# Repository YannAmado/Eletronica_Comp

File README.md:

# Projeto fonte com seletor de tensão
Yann Amado Nunes Costa : 10746943

Matéria : Eletrônica para Computação

Docente : Eduardo do Valles Simões

## Tabela de preços : 

| Peça                |  Preço              |
| ------------------- | ------------------- |
|  Transformador 220v-24v | R$41,00 |
|  Diodo 1N 4004 |  6xR$0,15 |
|       Capacitor 330uFx25V              |      R$0,34              |
|       Capacitor 470uFx25V              |      R$0,33              |
|       Capacitor 1.0uFx50V              |            3xR$0,10           |
|           Resistor 750Ohms          |      R$0,15               |
|           Resistor 150Ohms          |      R$0,20               |
|        LM317             |    R$7,50                 |
|   Potenciômetro Linear 1KΩ             |    R$1,99                 |

Obs : Os resistores foram escolhidos seguindo a formula provida pelo datasheet do LM317

## Simulação do Circuito no Falstad:

Imagem do circuito feito no falstad

link para o circuito : http://tinyurl.com/y8s6mfzf

## Esquemática e PCB

Todos os circuitos estão disponíveis dentro da página : https://github.com/YannAmado/Eletronica_Comp

- Imagem da esquemática feita no eagle

- Imagem do PCB feito no eagle

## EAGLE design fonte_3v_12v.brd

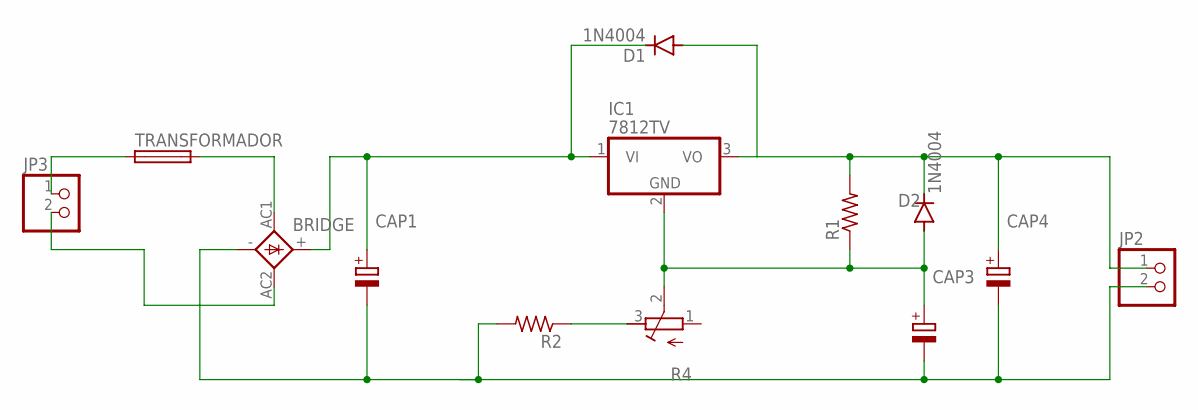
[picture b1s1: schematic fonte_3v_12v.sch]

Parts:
BRIDGE: 2KBB-R
CAP1, CAP3, CAP4: CPOL-EUE5-13; E5-13
D1, D2: 1N4004; DO41-10
IC1: 7812TV; TO220V
JP2, JP3: PINHD-1X2; 1X02
R1, R2: R-US_0204/7; 0204/7
R4: R-TRIMM3339P; RTRIM3339P
TRANSFORMADOR: SH22,5

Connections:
unnamed: JP3.1, TRANSFORMADOR.1
unnamed: BRIDGE.AC1, TRANSFORMADOR.2
unnamed: CAP4.+, D1.A, D2.C, IC1.3 (VO), JP2.1, R1.2
unnamed: BRIDGE.AC2, JP3.2
unnamed: BRIDGE.+, CAP1.+, D1.C, IC1.1 (VI)
unnamed: R2.1, R4.3 (E)
unnamed: BRIDGE.-, CAP1.-, CAP3.-, CAP4.-, JP2.2, R2.2
unnamed: CAP3.+, D2.A, IC1.2 (GND), R1.1, R4.2 (S)

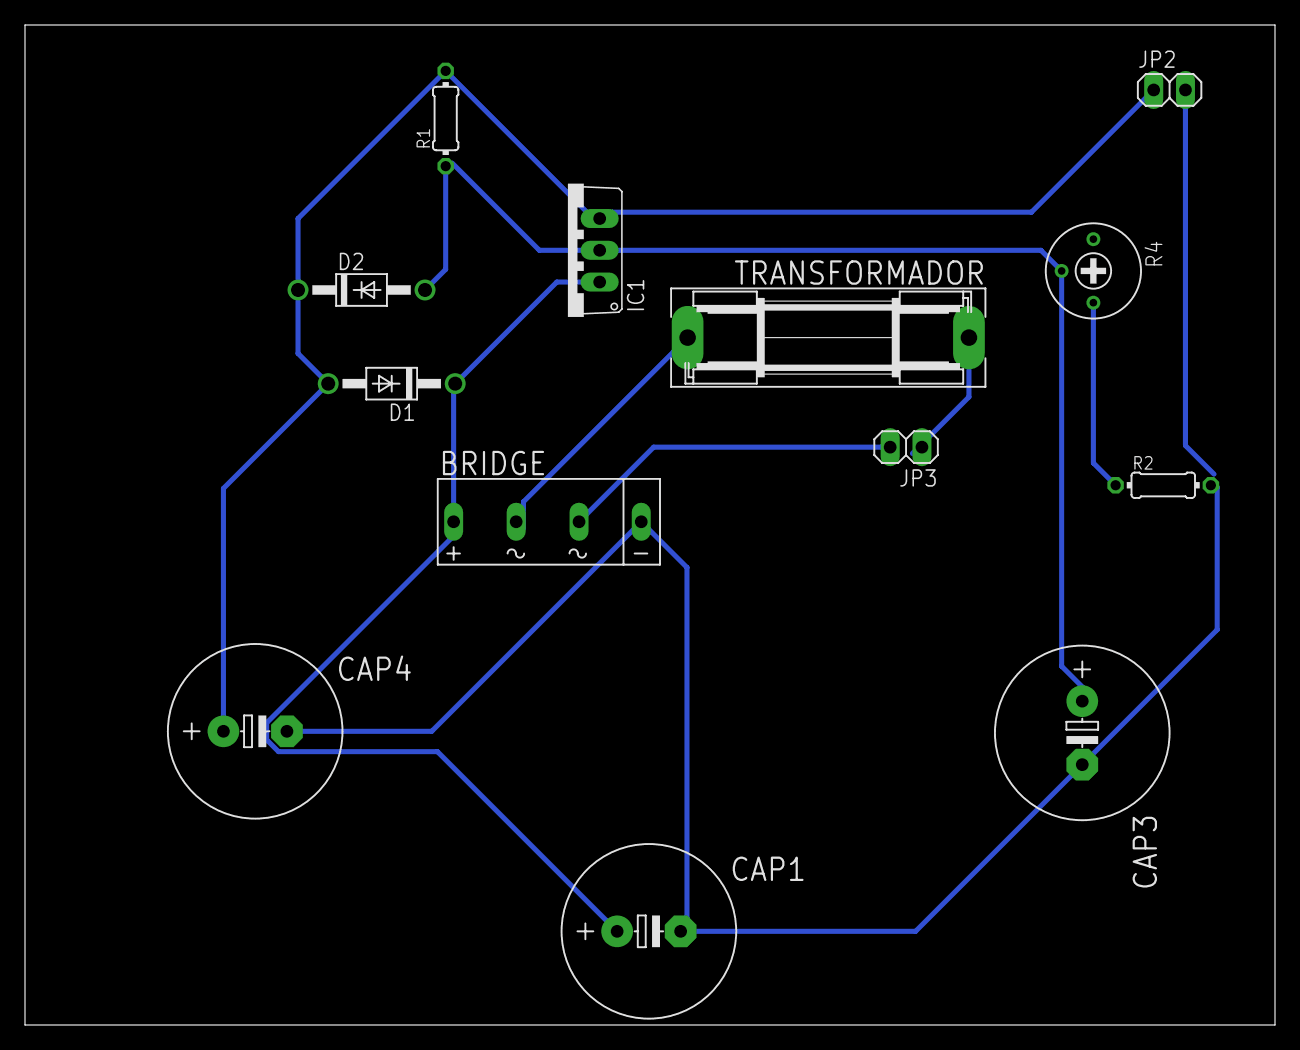
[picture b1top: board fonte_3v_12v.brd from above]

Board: 2 copper layers, 100.0 x 80.0 mm, 13 parts (0 on the bottom side), 8 nets.

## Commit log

2020-07-07 Create Fonte_12v_3v
